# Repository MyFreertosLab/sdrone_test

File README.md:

ESP32 ESP-IDF Drone
===================

This is a Drone Implementation with esp-idf and esp32.
This software is under construction

```
  git clone --recursive git@github.com:MyFreertosLab/sdrone.git
  idf.py build
  idf.py flash
```
<h1>State of the art</h1>
<p align="left">
  
  <p>Step 1: Minimal Hardware List</p>
</p>

1) The frame
2) RC TX/RX
3) PPM Encoder
4) IMU (mpu9250) with at least accelerometer and gyroscope
5) Battery
6) Esc (30Ah)
7) Motors
8) Propellers
9) The Board (a simple ESP32 board)
10) Cup of coffee

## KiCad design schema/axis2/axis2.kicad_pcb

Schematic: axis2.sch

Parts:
C1, C2: 100uF; CP_Radial_D5.0mm_P2.50mm
D1: D_ALT; D_DO-34_SOD68_P7.62mm_Horizontal
HS1: Heatsink_Pad_2Pin; Heatsink_Stonecold_HS-132_32x14mm_2xFixation1.5mm
J1: JA; PinSocket_2x10_P2.54mm_Vertical
J2: JB; PinSocket_2x10_P2.54mm_Vertical
J3: 5VPower; JST_XH_B2B-XH-AM_1x02_P2.50mm_Vertical
J4: 12VPower; BarrelJack_Wuerth_6941xx301002
J5: Power Motor 1; Deans; MPN 22-23-2021; Digi-Key_PN WM4200-ND
J6: Power Motor 2; Deans; MPN 22-23-2021; Digi-Key_PN WM4200-ND
J7: M1; PinHeader_1x03_P2.54mm_Horizontal
J8: M2; PinHeader_1x03_P2.54mm_Horizontal
J9: RC-PPM; PinHeader_1x03_P2.54mm_Horizontal
Q1: BC547; TO-92
RLY1: G5LE-14_DC5; Relay_SPDT_Omron-G5LE-1; MPN G5LE-14 DC5; Digi-Key_PN Z1011-ND
U1: gy-9250
U2: L7805; TO-220-3_Vertical
U3: axis2-frame; axis2-footprint

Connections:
+3V3: D1.1 (K), J1.1, RLY1.2 (COIL), U1.1 (vcc)
+5V: C2.1, J3.1, J9.2, U2.3 (OUT)
+12V: C1.1, J4.1, RLY1.1 (COM), U2.1 (IN)
+12VM: J5.1, J6.1, RLY1.4 (NC)
GND: C1.2, C2.2, J2.12, J3.2, J4.2, J5.2, J6.2, J7.1, J8.1, J9.1, Q1.3, U1.2 (gnd), U2.2 (GND)
GPIO32: J1.7, Q1.2
INT: J2.15, U1.8 (int)
M1S: J2.8, J7.3
M2S: J2.9, J8.3
MISO: J1.13, U1.7 (ado/miso)
MOSI: J1.15, U1.4 (sda/mosi)
NCS: J2.16, U1.9 (ncs)
unnamed: D1.2 (A), Q1.1, RLY1.5 (COIL)
RCS: J2.2, J9.3
SCL: J1.14, U1.3 (scl)

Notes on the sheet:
Power Motors
Power 12V
Power 5V
Controller Board
Motors Control

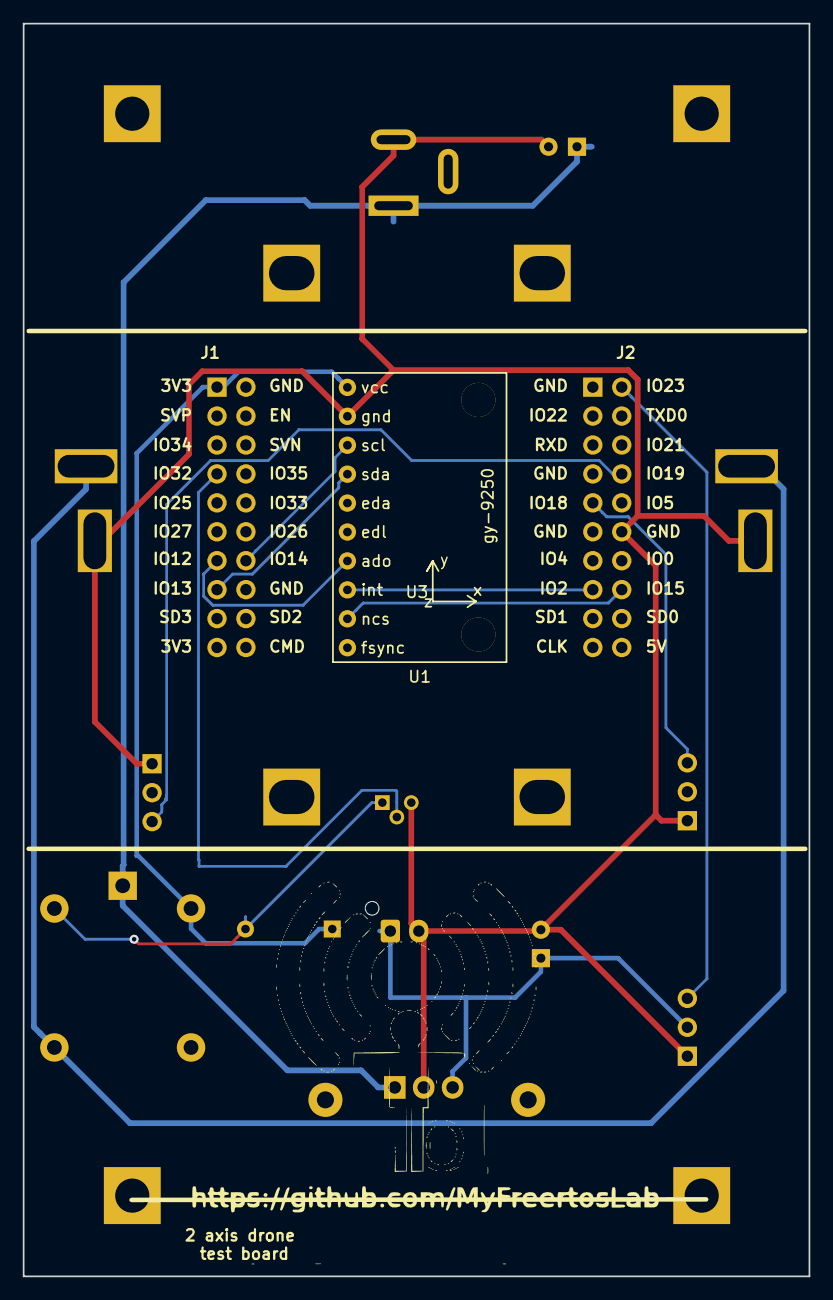
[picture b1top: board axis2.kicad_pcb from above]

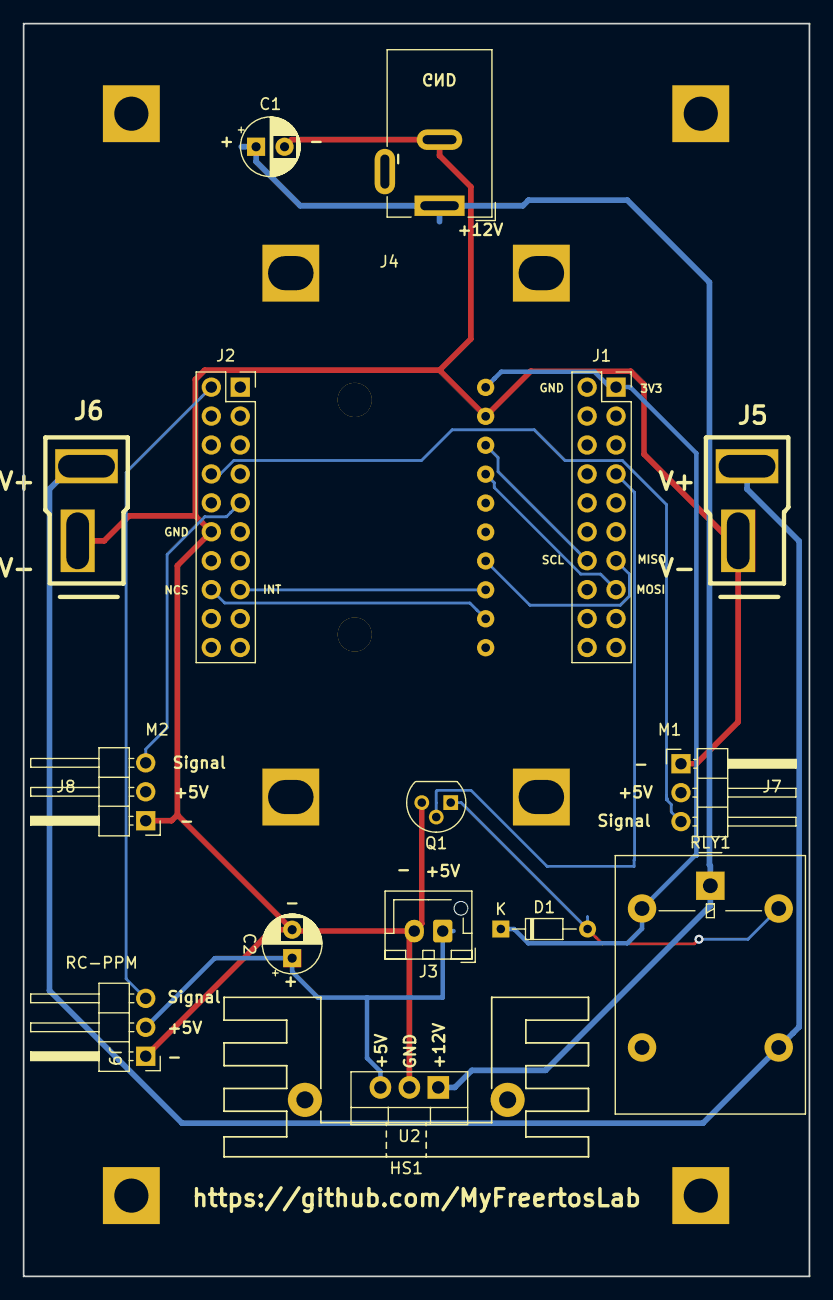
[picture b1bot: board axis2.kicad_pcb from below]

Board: 2 copper layers, 69.0 x 110.0 mm, 18 parts (16 on the bottom side), 15 nets.

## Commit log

2021-04-18 Primo Commit
2021-04-18 Aggiornato nome repo
2021-04-18 Aggiunto bozza api motors
2021-04-19 Aggiunto qualche test di prova
2021-04-24 Corretto scheda e testato relay per switch on/off motori. Implementato ciclo di switch on/off motori
2021-04-24 Modificato scheda aggiungendo BC547.
2021-05-15 Corretto scheda per errato posizionamento alimentazione esp32
2021-05-22 Iniziato ad integrare imu ed rc
2021-05-24 Tolto media dai sample del giroscopio, inserito dati di calibrazione corretti
2021-05-24 Modificato schema per inversione relè e connettori alimentazione motori
2021-05-29 Iniziato implementazione per normalizzazione dati raw RC
2021-05-31 Lettura dati calibrazione da NVS
2021-05-31 Collegato per prova un motore a RC e formulato conversione Throttle->Thrust (Newton) e Thrust->Duty(percentuale 52%->100%). Previsto una Dead Zone tra 52% e 60% del duty
2021-06-01 Quando RC non è collegato, il controller invia ai motori dati thrust non inizializzati. Corretto il problema, ma sono da rivedere le api delle componenti in modo che l'inizializzazione sia sempre a c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
2021-06-01 - Il controller deve partire solo se riceve la notifica dail main. - Spostato l'inizializzazione del Throttle su task RC in modo che questo sia comunicato sempre nell'intervallo [0,SDRONE_RC_CHANNEL_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
2021-06-02 Aggiunto componente ina3221 e iniziato sviluppo
2021-06-03 Completato supporto INA3221 e inserito codice di test (poi da togliere) per rilevare dati Bus e Shunt Voltage con tre motori collegati
2021-06-05 Modificato valori R e P del Kalman Filter. Corrispondono alla varianza ed all'errore iniziale in presenza di eliche
2021-06-05 Inserito printf di debug per testare rpy con dati filtrati da filtro di kalman.
2021-06-05 Rimesso ciclo di programmazione ESC in startup
2021-06-07 Prima impostazione semplice controller
2021-06-08 Fixed controller for 2 propellers.
2021-06-12 Aggiunto bozza processo di misurazione
2021-06-12 Corretto errore previsione
2021-06-13 Previsioni corrispondenti al comportamento reale del sistema
2021-06-13 Aggiunto compensazione Proporzionale. Mancano integrale e derivata
2021-06-13 Bozza di PID ... tutta da rivedere ...
2021-06-15 Sospeso implementazione PID. Devo rivedere i rapporti dPropellers e dAlfa
2021-06-16 Aggiunto calcolo alfa su gyro ed aggiunto errAlfa proporzionale in correzione sulla response
2021-06-18 Aggiunto fattore di reattività e Response Gain
2021-06-21 Tuning ke e fattore di proporzionalità alfa->pwm (response gain)
2021-07-11 Ridotto oscillazioni Da provare con RC
2021-07-13 Raddoppiato filtro U in ingresso
2021-07-14 Uscita Controller pari a 0.25 alfa, tolto response gain ed aumentato a 0.5 il fattore dell'errore su alfa. Converge più rapidamente
2021-07-16 Tolto kd e ki non hanno senso qui
